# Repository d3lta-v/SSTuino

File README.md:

Designed by FourierIndustries LLP | Designed, assembled and tested in Singapore

# SSTuino

SSTuino is an easy to use Wi-Fi enabled microcontroller, designed and fabricated by SST Alumni. Users can write programs to connect or control things over the Internet. It is derived from the SPEEEduino 1.1 with some improvements.

**SSTuino Official Website: [https://sstuino.fourier.industries](https://sstuino.fourier.industries)**

Related projects:

* [SSTuino Companion Library](https://github.com/d3lta-v/SSTuino_Companion)
* [Ultra Light Wi-Fi Interface](https://github.com/d3lta-v/ULWI)
* [ESPblaster](https://github.com/d3lta-v/ESPblaster)

## Technical information

### Repository Layout

* **SSTuino**: EAGLE files for SSTuino
* **Image Assets**: Image assets for websites related to the SSTuino and markdown pages.

### Startup states table

This table controls the various startup states of the ESP8266-01 Wi-Fi module, which allows it to operate, or be reprogrammed with your custom firmware, or even be electrically isolated from the rest of the SSTuino entirely.

|  | GPIO0 (1) | GPIO2 (2) | ESP-RX connect to D4 (3) | ESP-TX connect to D2 (4) | ESP-RESET Button |
|---------|:---------:|:---------:|:---------:|:---------:|:---------:|
| Wi-Fi Enable | ⬆️ | ⬆️ | ⬆️ | ⬆️ | Leave open |
| Disconnect ESP-01 | ❎ | ❎ | ⬇️ | ⬇️ | Leave open |
| Reset ESP-01 | ❎ | ❎ | ❎ | ❎ | Press down |
| Flash ESP-01 | ⬇️ | ⬆️ | ⬇️ | ⬇️ | Press down, set switches, release |

## Contributing

Contributing to the SSTuino Git Repository requires you to have EAGLE 8.4 or newer which supports Managed Libraries.

SSTuino primarily uses EAGLE's Managed Libraries made by Sparkfun, but also contain our own custom footprints and SMD component footprints from Cytron.

## Our team

* Chief Designer: Pan Ziyue ([@sammy0025](https://twitter.com/sammy0025))
* Assistants/Advisers: Goh Qian Zhe ([@QianZheGoh](https://twitter.com/QianZheGoh))
* The awesome folks at Arduino, Sparkfun and Adafruit for technical reference and ECAD models.

Open Source Hardware (OSHW)

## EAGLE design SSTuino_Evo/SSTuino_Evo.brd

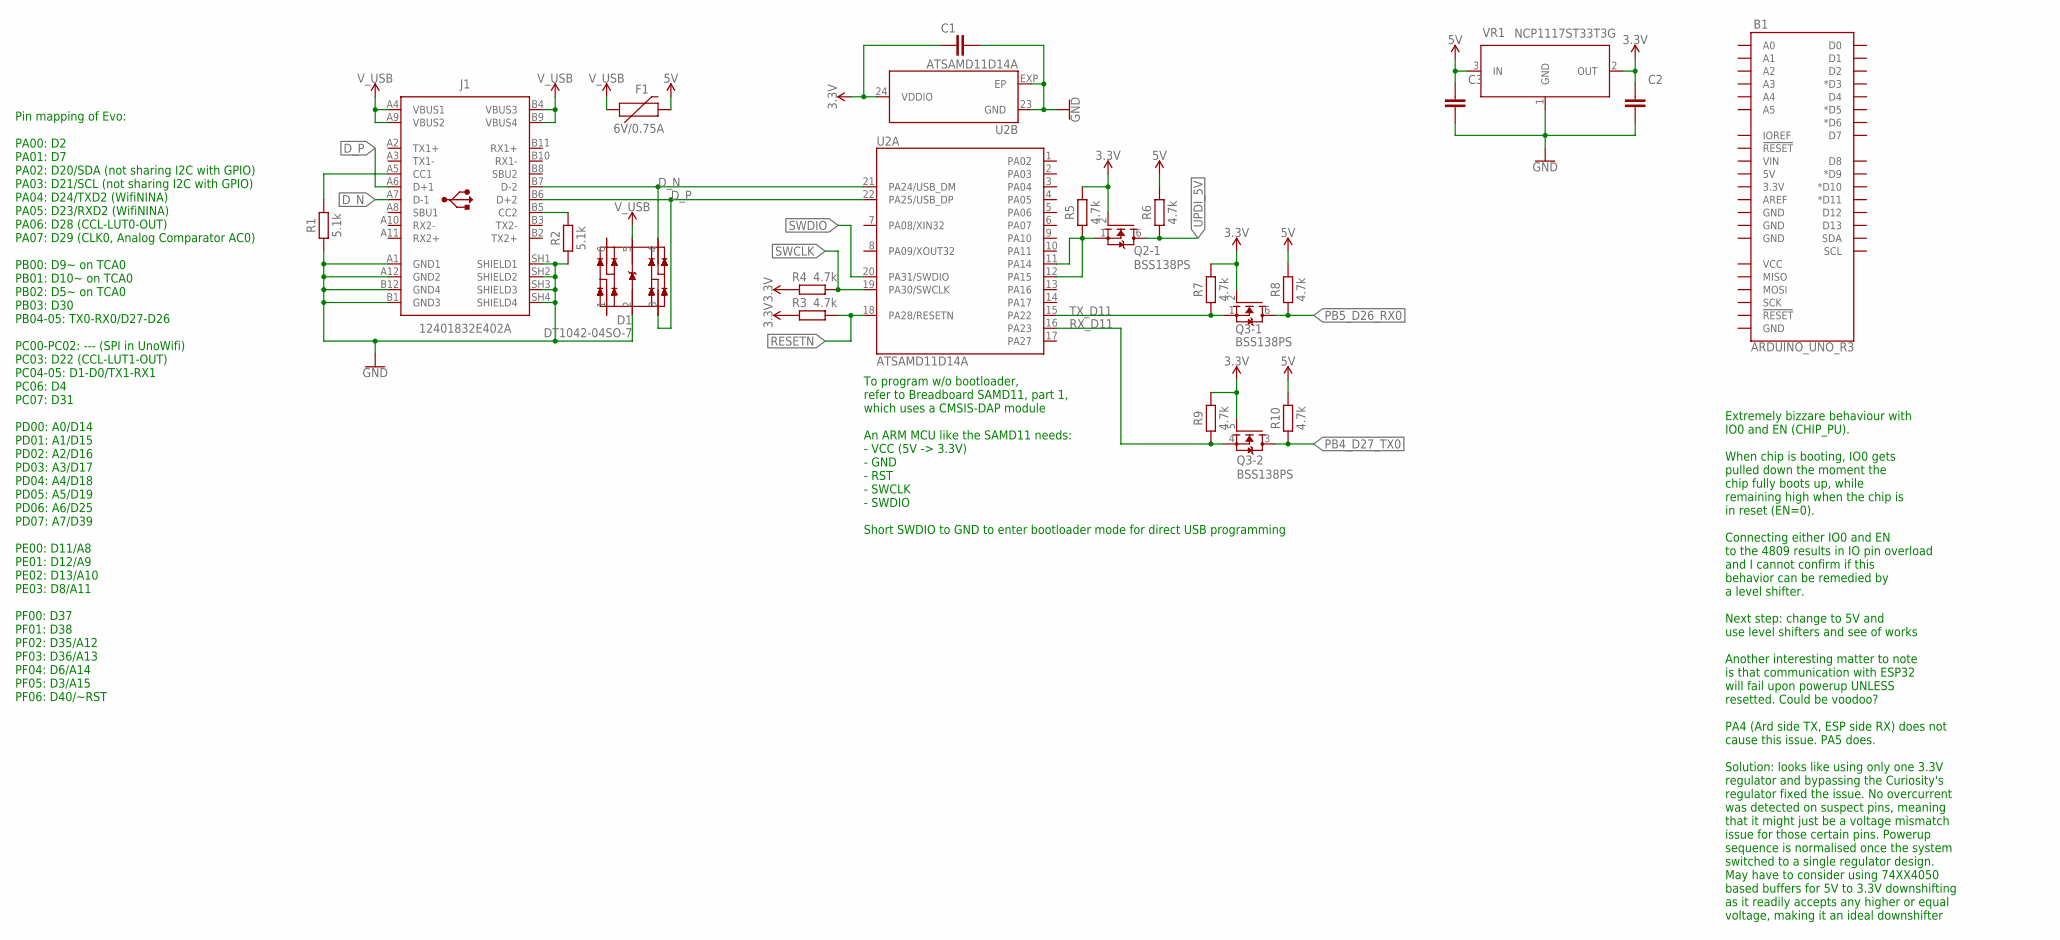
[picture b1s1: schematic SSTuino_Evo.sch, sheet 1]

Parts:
B1: ARDUINO_UNO_R3; ARDUINO_R3
C1: 100n; CAPC1005X60
C2, C3: 10uF; CAPC1608X85
D1: DT1042-04SO-7; SOT95P285X140-6N
F1: 6V/0.75A; 1206
J1: 12401832E402A
Q2, Q3: BSS138PS; ARDUINO-TRANSISTORS_SOT363
R1, R2: 5.1k; RESC1005X40
R3, R4, R5, R6, R7, R8, R9, R10: 4.7k; RESC1005X40
U2: ATSAMD11D14A; ARDUINO-UCS&SOCS_HVQFN24
VR1: NCP1117ST33T3G; SOT230P700X170-4

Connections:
3.3V: C1.1, C2.1, Q2.2 (G), Q3.2 (G), Q3.5 (G), R3.2, R4.2, R5.2, R7.2, R9.2, U2.24 (VDDIO), VR1.2 (OUT); also elsewhere on the board
5V: C3.1, F1.2, R6.2, R8.2, R10.2, VR1.3 (IN); also elsewhere on the board
CC1: J1.A5 (CC1), R1.2
CC2: J1.B5 (CC2), R2.2
D_N: D1.4 (IO3), J1.A7 (D-1), J1.B7 (D-2), U2.21 (PA24/USB_DM)
D_P: D1.3 (IO2), J1.A6 (D+1), J1.B6 (D+2), U2.22 (PA25/USB_DP)
GND: C1.2, C2.2, C3.2, D1.2 (VSS), J1.A1 (GND1), J1.A12 (GND2), J1.B1 (GND3), J1.B12 (GND4), J1.SH1 (SHIELD1), J1.SH2 (SHIELD2), J1.SH3 (SHIELD3), J1.SH4 (SHIELD4), R1.1, R2.1, U2.23 (GND), U2.EXP (EP), VR1.1 (GND); also elsewhere on the board
PB4_D27_TX0: Q3.3 (D), R10.1; also elsewhere on the board
PB5_D26_RX0: Q3.6 (D), R8.1; also elsewhere on the board
RESETN: R3.1, U2.18 (PA28/RESETN)
RX_D11: Q3.4 (S), R9.1, U2.16 (PA23)
SWCLK: R4.1, U2.19 (PA30/SWCLK)
SWDIO: U2.20 (PA31/SWDIO)
TX_D11: Q3.1 (S), R7.1, U2.15 (PA22)
UPDI_3V3: Q2.1 (S), R5.1, U2.11 (PA14), U2.12 (PA15)
UPDI_5V: Q2.6 (D), R6.1
V_USB: D1.5 (VCC), F1.1, J1.A4 (VBUS1), J1.A9 (VBUS2), J1.B4 (VBUS3), J1.B9 (VBUS4)

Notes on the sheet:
Pin mapping of Evo: PA00: D2 PA01: D7 PA02: D20/SDA (not sharing I2C with GPIO) PA03: D21/SCL (not sharing I2C with GPIO) PA04: D24/TXD2 (WifiNINA) PA05: D23/RXD2 (WifiNINA) PA06: D28 (CCL-LUT0-OUT) PA07: D29 (CLK0, Analog Comparator AC0) PB00: D9~ on TCA0 PB01: D10~ on TCA0 PB02: D5~ on TCA0 PB03: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
To program w/o bootloader, refer to Breadboard SAMD11, part 1, which uses a CMSIS-DAP module An ARM MCU like the SAMD11 needs: - VCC (5V -> 3.3V) - GND - RST - SWCLK - SWDIO Short SWDIO to GND to enter bootloader mode for direct USB programming
Extremely bizzare behaviour with IO0 and EN (CHIP_PU). When chip is booting, IO0 gets pulled down the moment the chip fully boots up, while remaining high when the chip is in reset (EN=0). Connecting either IO0 and EN to the 4809 results in IO pin overload and I cannot confirm if this behavior can 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

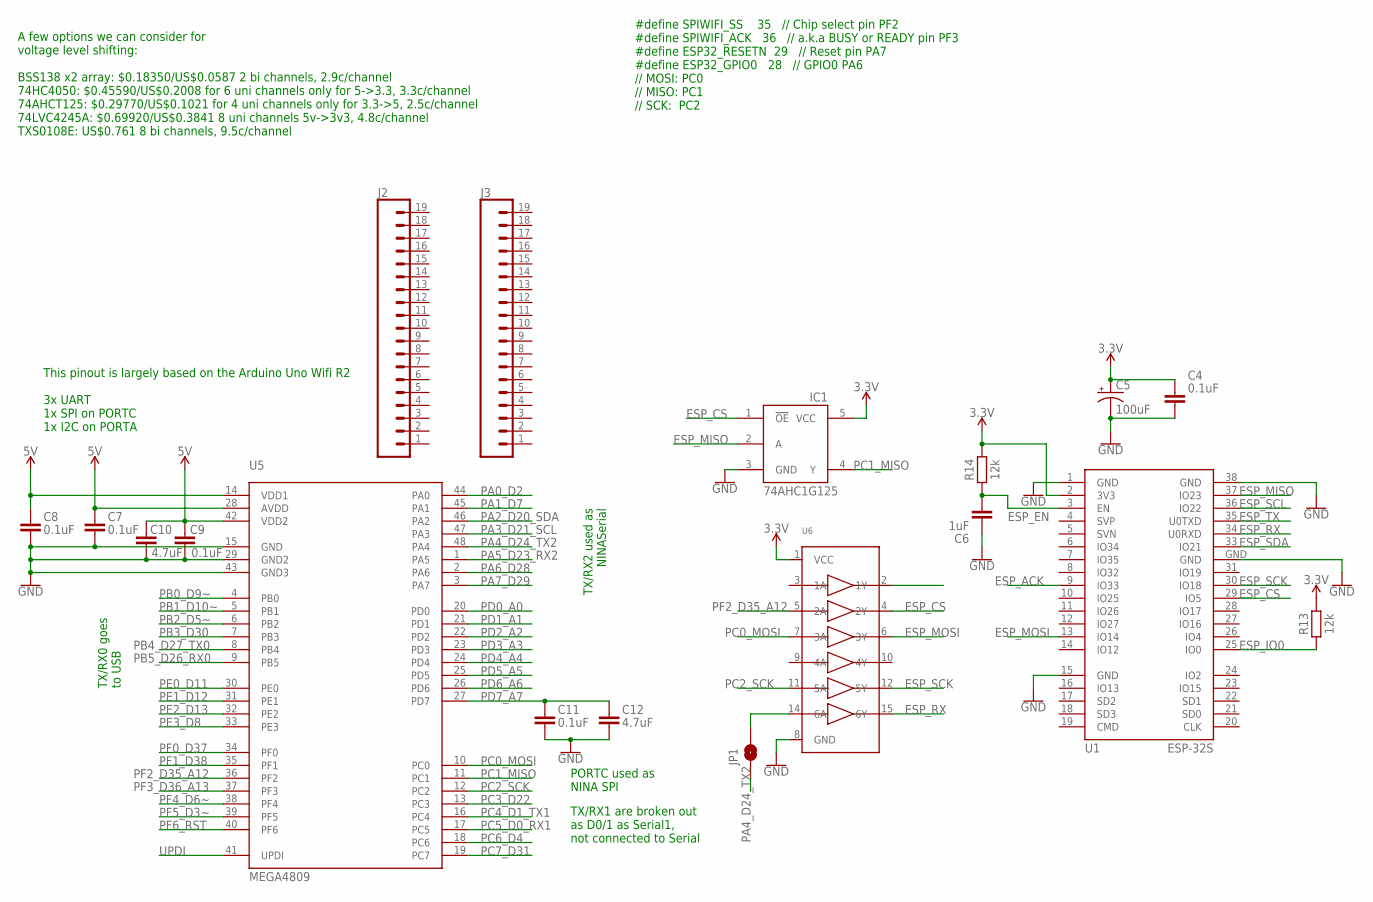
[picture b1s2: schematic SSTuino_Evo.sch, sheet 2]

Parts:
C4, C7, C8, C9, C11: 0.1uF; CAPC1005X60
C5: 100uF; CAPMP3216X180N
C6: 1uF; CAPC1005X60
C10, C12: 4.7uF; CAPC1005X60
IC1: 74AHC1G125; SOT23-5L
J2, J3: CONN_191X19_NO_SILK; 1X19_NO_SILK
JP1: JUMPER-SMT_2_NO_SILK; SMT-JUMPER_2_NO_SILK
R13, R14: 12k; RESC1005X40
U1: ESP-32S
U5: MEGA4809; TQFP48
U6: 74HC4050DTSSOP; TSSOP16

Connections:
3.3V: C4.1, C5.1 (+), IC1.5 (VCC), R13.2, R14.2, U1.2 (3V3), U6.1 (VCC); also elsewhere on the board
5V: C7.1, C8.1, C9.1, C10.1, U5.14 (VDD1), U5.28 (AVDD), U5.42 (VDD2); also elsewhere on the board
ESP_ACK: U1.9 (IO33)
ESP_CS: IC1.1 (!OE), U1.29 (IO5), U6.4 (2Y)
ESP_EN: C6.2, R14.1, U1.3 (EN)
ESP_IO0: R13.1, U1.25 (IO0)
ESP_MISO: IC1.2 (A), U1.37 (IO23)
ESP_MOSI: U1.13 (IO14), U6.6 (3Y)
ESP_RX: U1.34 (U0RXD), U6.15 (6Y)
ESP_SCK: U1.30 (IO18), U6.12 (5Y)
ESP_SCL: U1.36 (IO22)
ESP_SDA: U1.33 (IO21)
ESP_TX: U1.35 (U0TXD)
GND: C4.2, C5.2 (-), C6.1, C7.2, C8.2, C9.2, C10.2, C11.2, C12.2, IC1.3 (GND), U1.1 (GND), U1.15 (GND), U1.38 (GND), U1.GND, U5.15 (GND), U5.29 (GND2), U5.43 (GND3), U6.8 (GND); also elsewhere on the board
unnamed: JP1.2, U6.14 (6A)
PA0_D2: U5.44 (PA0)
PA1_D7: U5.45 (PA1)
PA2_D20_SDA: U5.46 (PA2)
PA3_D21_SCL: U5.47 (PA3)
PA4_D24_TX2: JP1.1, U5.48 (PA4)
PA5_D23_RX2: U5.1 (PA5)
PA6_D28: U5.2 (PA6)
PA7_D29: U5.3 (PA7)
PB0_D9~: U5.4 (PB0)
PB1_D10~: U5.5 (PB1)
PB2_D5~: U5.6 (PB2)
PB3_D30: U5.7 (PB3)
PB4_D27_TX0: U5.8 (PB4); also elsewhere on the board
PB5_D26_RX0: U5.9 (PB5); also elsewhere on the board
PC0_MOSI: U5.10 (PC0), U6.7 (3A)
PC1_MISO: IC1.4 (Y), U5.11 (PC1)
PC2_SCK: U5.12 (PC2), U6.11 (5A)
PC3_D22: U5.13 (PC3)
PC4_D1_TX1: U5.16 (PC4)
PC5_D0_RX1: U5.17 (PC5)
PC6_D4: U5.18 (PC6)
PC7_D31: U5.19 (PC7)
PD0_A0: U5.20 (PD0)
PD1_A1: U5.21 (PD1)
PD2_A2: U5.22 (PD2)
PD3_A3: U5.23 (PD3)
PD4_A4: U5.24 (PD4)
PD5_A5: U5.25 (PD5)
PD6_A6: U5.26 (PD6)
PD7_A7: C11.1, C12.1, U5.27 (PD7)
PE0_D11: U5.30 (PE0)
PE1_D12: U5.31 (PE1)
PE2_D13: U5.32 (PE2)
PE3_D8: U5.33 (PE3)
PF0_D37: U5.34 (PF0)
PF1_D38: U5.35 (PF1)
PF2_D35_A12: U5.36 (PF2), U6.5 (2A)
PF3_D36_A13: U5.37 (PF3)
PF4_D6~: U5.38 (PF4)
PF5_D3~: U5.39 (PF5)
PF6_RST: U5.40 (PF6)
UPDI: U5.41 (UPDI)

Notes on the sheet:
A few options we can consider for voltage level shifting: BSS138 x2 array: $0.18350/US$0.0587 2 bi channels, 2.9c/channel 74HC4050: $0.45590/US$0.2008 for 6 uni channels only for 5->3.3, 3.3c/channel 74AHCT125: $0.29770/US$0.1021 for 4 uni channels only for 3.3->5, 2.5c/channel 74LVC4245A: $0.69920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
This pinout is largely based on the Arduino Uno Wifi R2 3x UART 1x SPI on PORTC 1x I2C on PORTA
TX/RX2 used as NINASerial
PORTC used as NINA SPI
TX/RX1 are broken out as D0/1 as Serial1, not connected to Serial
TX/RX0 goes to USB
#define SPIWIFI_SS 35 // Chip select pin PF2 #define SPIWIFI_ACK 36 // a.k.a BUSY or READY pin PF3 #define ESP32_RESETN 29 // Reset pin PA7 #define ESP32_GPIO0 28 // GPIO0 PA6 // MOSI: PC0 // MISO: PC1 // SCK: PC2

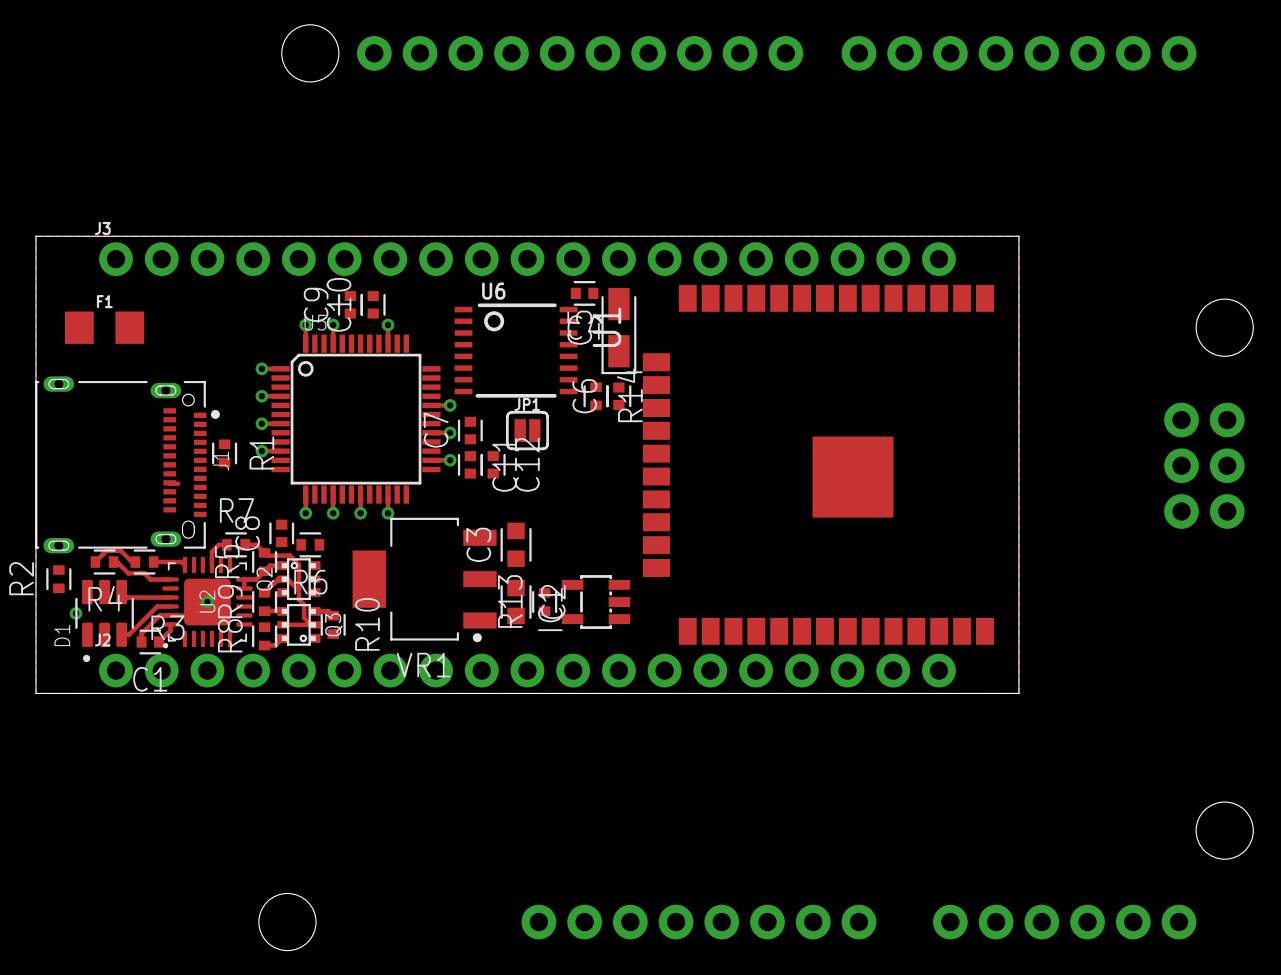
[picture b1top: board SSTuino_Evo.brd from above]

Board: 2 copper layers, 54.6 x 25.4 mm, 39 parts (0 on the bottom side), 30 nets.

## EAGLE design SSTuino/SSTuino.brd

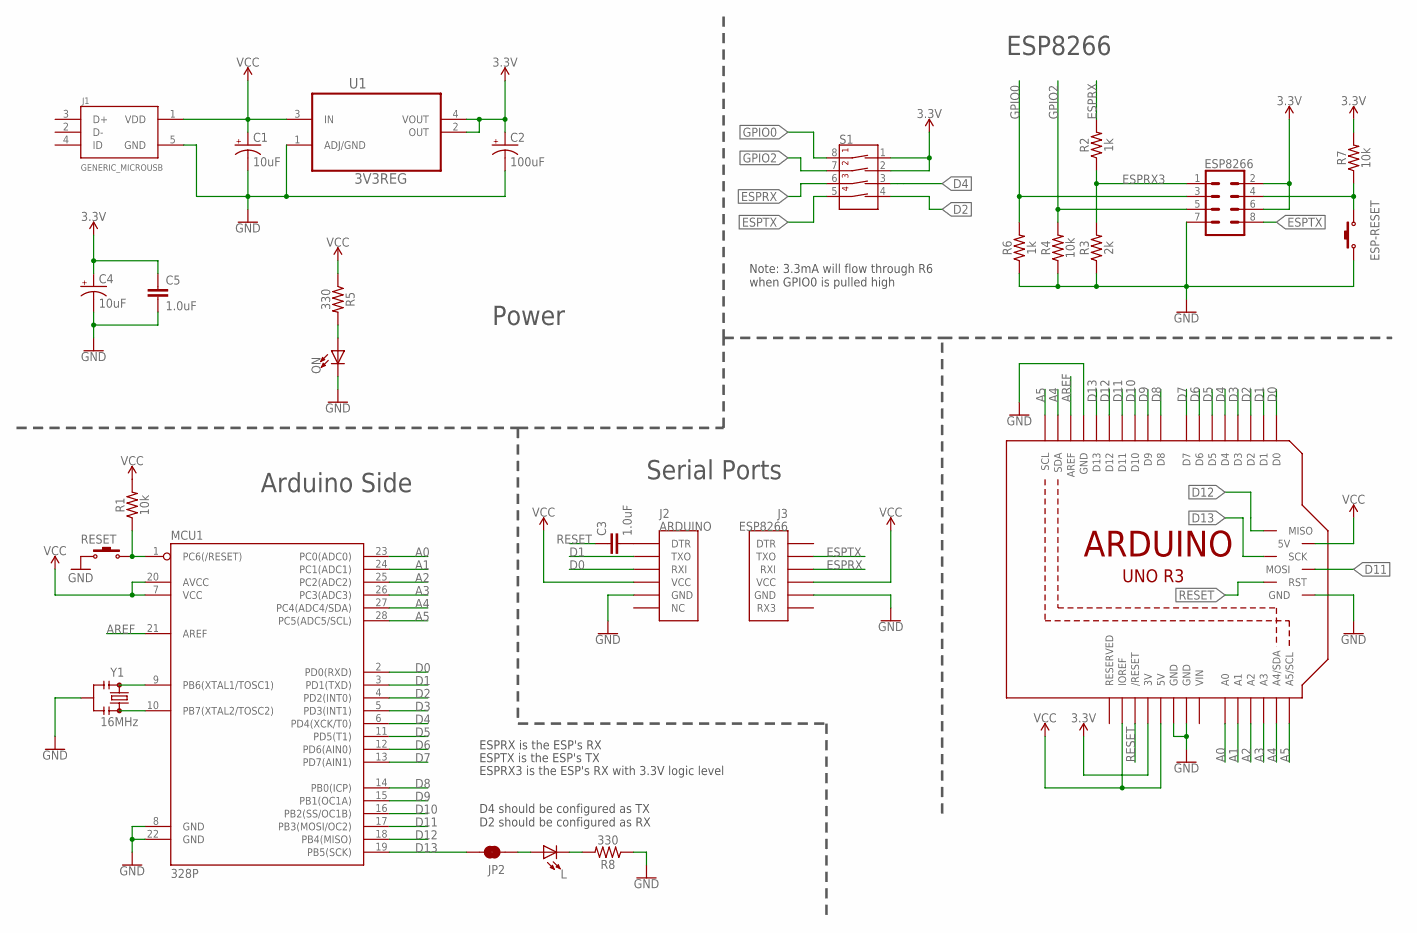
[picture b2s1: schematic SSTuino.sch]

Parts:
C1: 10uF; EIA3528
C2: 100uF; PANASONIC_D
C3, C5: 1.0uF; 1206
C4: 10uF; EIA3216
ESP8266: CONN_04X2; 2X4
ESP-RESET: SW-PB_(KAN0641); S-SP-4N-KAN0641
J1: GENERIC_MICROUSB; FRAMATOME_10118194-0001LF
J2: ARDUINO; CP2102_DEVICE_MICROUSB
J3: ESP8266; CP2102_DEVICE_MICROUSB_ESP8266
JP2: JUMPER-SMT_2_NC_TRACE_SILK; SMT-JUMPER_2_NC_TRACE_SILK
L: LED3MM
M1: ARDUINO_R3_ICSPSST; ARDUINOR3_ISCP_SST
MCU1: 328P; DIP28
ON: LED3MM
R1, R4, R7: 10k; 1206
R2, R6: 1k; 1206
R3: 2k; 1206
R5, R8: 330; 1206
RESET: SW-PB_(KAN0641); S-SP-4N-KAN0641
S1: DIP-04SMD; DIPSWITCH-04-SMD
U1: 3V3REG; SOT230P696X180-4N
Y1: 16MHz; RESONATOR-SMD-3.2X1.3

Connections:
3.3V: C2.+, C4.+, C5.1, ESP8266.2, ESP8266.6, M1.3V, R7.2, S1.1 (1A), S1.2 (2A), U1.2 (OUT), U1.4 (VOUT)
A0: M1.A0, MCU1.23 (PC0(ADC0))
A1: M1.A1, MCU1.24 (PC1(ADC1))
A2: M1.A2, MCU1.25 (PC2(ADC2))
A3: M1.A3, MCU1.26 (PC3(ADC3))
A4: M1.A4 (A4/SDA), M1.SDA, MCU1.27 (PC4(ADC4/SDA))
A5: M1.A5 (A5/SCL), M1.SCL, MCU1.28 (PC5(ADC5/SCL))
AREF: M1.AREF, MCU1.21 (AREF)
D0: J2.RXI, M1.D0, MCU1.2 (PD0(RXD))
D1: J2.TXO, M1.D1, MCU1.3 (PD1(TXD))
D2: M1.D2, MCU1.4 (PD2(INT0)), S1.4 (4A)
D3: M1.D3, MCU1.5 (PD3(INT1))
D4: M1.D4, MCU1.6 (PD4(XCK/T0)), S1.3 (3A)
D5: M1.D5, MCU1.11 (PD5(T1))
D6: M1.D6, MCU1.12 (PD6(AIN0))
D7: M1.D7, MCU1.13 (PD7(AIN1))
D8: M1.D8, MCU1.14 (PB0(ICP))
D9: M1.D9, MCU1.15 (PB1(OC1A))
D10: M1.D10, MCU1.16 (PB2(SS/OC1B))
D11: M1.D11, M1.MOSI, MCU1.17 (PB3(MOSI/OC2))
D12: M1.D12, M1.MISO, MCU1.18 (PB4(MISO))
D13: JP2.2, M1.D13, M1.SCK, MCU1.19 (PB5(SCK))
DTR: C3.2, J2.DTR
ESPRESET: ESP8266.4, ESP-RESET.3 (2), ESP-RESET.4 (2), R7.1
ESPRX: J3.P$4 (RXI), R2.2, S1.6 (3B)
ESPRX3: ESP8266.1, R2.1, R3.2
ESPTX: ESP8266.8, J3.P$3 (TXO), S1.5 (4B)
GND: C1.C (-), C2.-, C4.-, C5.2, ESP8266.7, ESP-RESET.1, ESP-RESET.2 (1), J1.5 (GND), J2.GND, J3.P$5 (GND), M1.GND, M1.GND@1 (GND), M1.GND@2 (GND), M1.GND@3 (GND), MCU1.8 (GND), MCU1.22 (GND), ON.K (C), R3.1, R4.1, R6.1, R8.1, RESET.1, RESET.2 (1), U1.1 (ADJ/GND), Y1.2
GPIO0: ESP8266.3, R6.2, S1.8 (1B)
GPIO2: ESP8266.5, R4.2, S1.7 (2B)
unnamed: MCU1.10 (PB7(XTAL2/TOSC2)), Y1.3
unnamed: L.K (C), R8.2
unnamed: JP2.1, L.A
unnamed: ON.A, R5.2
unnamed: MCU1.9 (PB6(XTAL1/TOSC1)), Y1.1
RESET: C3.1, M1.RESET (/RESET), M1.RESET_ICSP (RST), MCU1.1 (PC6(/RESET)), R1.1, RESET.3 (2), RESET.4 (2)
VCC: C1.A (+), J1.1 (VDD), J2.5V (VCC), J3.P$6 (VCC), M1.5V, M1.5V_ICSP (5V), M1.IOREF, MCU1.7 (VCC), MCU1.20 (AVCC), R1.2, R5.1, U1.3 (IN)
VIN: M1.VIN

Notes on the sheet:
ESPRX is the ESP's RX
ESPTX is the ESP's TX
D4 should be configured as TX D2 should be configured as RX
ESPRX3 is the ESP's RX with 3.3V logic level
Power
Arduino Side
Serial Ports
ESP8266
Note: 3.3mA will flow through R6 when GPIO0 is pulled high

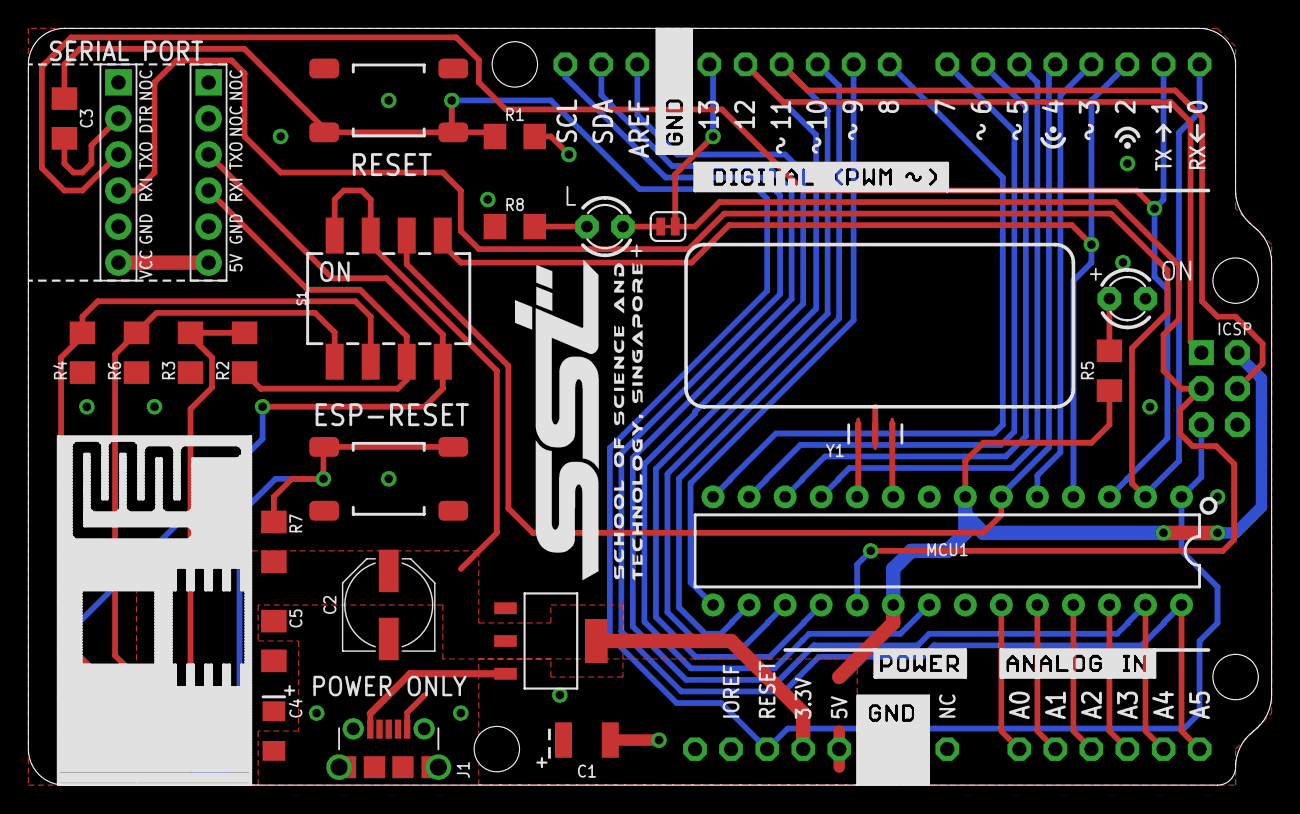
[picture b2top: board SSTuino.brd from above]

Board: 2 copper layers, 87.6 x 53.3 mm, 30 parts (0 on the bottom side), 37 nets.

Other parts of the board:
U$1: ESP8266-NEGASILK
U$2: SST-MED
U$3: SST-HEXAGON-INV-BMP

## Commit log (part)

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2019-07-01 added analytics to page
2019-07-01 added global site tag
2019-07-03 created thunkable.md for lessons involving thunkable
2019-07-03 test
2019-07-03 updated thunkable.md with content
2019-07-03 updated content for thunkable.md
2019-07-03 added tinkercad.md
2019-07-03 updated content of tinkercad.md
2019-07-03 minor update to content of tinkercad.md
2019-07-03 edits made to the content of thunkable.md
2019-07-03 minor update to content in thunkable.md
2019-07-03 minor updates to tinkercad.md
2019-07-03 updated content from helloWorld.md
2019-07-03 upload of media for tinkercad tutorial
2019-07-03 fixed broken picture link for Social Provider segment
2019-07-03 attempt to fix broken lists
2019-07-03 fixed image sizing for sign in and social provider images
2019-07-03 fixed errata of list
2019-07-03 asdhapsdhaosdi
2019-07-05 minor formatting to content in temperature sensor section
2019-07-05 updated content for helloWorld.md
2019-07-05 minor update to formatting for helloWorld.md
2019-07-05 drafted new content headings in index.md
2019-07-08 added post.html for prototyping of tutorial pages
2019-07-08 updated header to new format
2019-07-08 trying out new layouts for tutorial pages
2019-07-08 fixed missing body and html tags at the bottom of the code
2019-07-08 deleted post.html and reverted formatting of addButton.md to last edit.
2019-07-08 created lessonIntro.md
2019-07-08 Updated index.md with new content (Link to lessonIntro.md)
2019-07-08 corrected erronus name
2019-07-08 creation of thunkableIntro.md, change of content in index and addition of assets
2019-07-08 Addition of assets for tutorial
2019-07-08 addition of image assets for thunkableIntro.md
2019-07-08 updated link for index.md
2019-07-08 updated image formatting in thunkableIntro.md
2019-07-08 creation of image assets
2019-07-08 insert images to thunkableIntro.md
2019-07-08 edited formatting of pictures
2019-07-08 fixed error in picture link
2019-07-08 edited formatting for image assets in thunkableIntro.md
2019-07-08 Updated content of thunkableIntro.md
2019-07-08 edited content in thunkableIntro.md
2019-07-08 Updated content in thunkableIntro.md
2019-07-08 creation of thunkableSpicing.md
2019-07-08 added electronicBasics.md and edited content of tinkercad.md
2019-07-08 minor edits to formatting
2019-07-08 added content in electronicBasics.md
2019-07-08 updated content and formatting of electronicBasics.md
2019-07-08 added link to electronicBasics.html in index.md
2019-07-08 updated content of electronicBasis.md
2019-07-08 updated formatting for attached image asset
2019-07-10 updated content in tinkercad.d
2019-07-10 added link to index.md
2019-07-10 updated content for electronicBasics.md with a gif from sparkfun lmao
2019-07-10 updated content for electronicBasics.md
2019-07-10 added content to electronicBasics.md
2019-07-11 fixed error in link
2019-07-12 Updated content for tinkercad.md
2019-07-15 Moved content from partsList.md to electronicBasics.md to reduce confusion in the future.
2019-07-15 added content from partsList.md to reduce confusion
2019-07-16 Updated content and testing out linking headers
2019-07-16 edited resistor content in electronicBasics.md
2019-07-16 Shifted breadboard content
2019-07-16 testing of headers
2019-07-16 fixed header link for LED
2019-07-16 Reorganised content in electronicBasics.md
2019-07-16 Updated table of contents for electronicBascis.md
2019-07-16 fixed error in header link
2019-07-16 lmao
2019-07-16 Updated index.md to include a interest form
2019-07-16 Updated formatting for link in index.md
2019-07-16 Updated content for supportr and contace
2019-07-16 removed section about changes
2019-07-16 Upload of resistor pictures
2019-07-16 Insertion of media for metal and carbon resistor comparison
2019-07-17 Upload of image assets for tutorial
2019-07-17 Updated content of electronicBasics.md
2019-07-17 Updated content in electronicBasics.md
2019-07-17 updated for useful Links page
2019-07-17 updated links for links
2019-07-17 Updated content for links.md
2019-07-18 updated links.md
2019-07-18 Upload of image assets
2019-07-18 Updated content in tinkercad.md
2019-07-18 Updated errenous picture links in tinkercad.md
2019-07-18 Updated content and formatting for tinkercad.md
2019-07-18 Updated content of sstuinoProgram.md
2019-07-18 Updated index.md to include the new sstuinoProgram.md link
2019-07-18 Updated tinkercad.md with link to sstuinoProgram.md
2019-07-18 fixed broken link
2019-07-18 SSTuino preview updated
2019-07-19 Updated content for sstuinoProgram.md
2019-07-19 Updated content in sstuinoProgram.md
2019-07-19 Removed Sec1 index menu, due to tutorials being replaced
2019-07-19 update of content
2019-07-19 updated content for digitalRead.md
2019-07-19 fixed missing image asset in sstuinoProgram.md
2019-07-19 fixed bad formatting
2019-07-19 Updated digitalRead.md
2019-07-22 gif test
2019-07-22 Addition of gif for the tutorial
2019-07-22 fixed an error in formatting
2019-07-22 removal of redundant sec 1 index
2019-07-22 Update of media content
2019-07-22 Updated formatting for digitalRead.md
2019-07-22 Fixed bad formatting in digitalRead.md
2019-07-23 Update README.md
    Changed link for reference website to SSTuino Website
2019-07-23 Updated content for index.md
2019-07-24 Updated formatting
2019-07-24 Upload of media assets
2019-07-24 Wrote the basics of AND and OR operators and how they came about
2019-07-24 changed sentence and added logic gate link
2019-07-25 decided not to use B612 for development due to lack of slash with digit "0"
2019-07-25 updated content in digitalRead.md
2019-07-25 fixed wrong image asset in digitalRead.md
2019-08-01 updated content of digitalRead.md
2019-08-02 Updated content for digitalWrite.md
2019-08-02 create media content
2019-08-03 Add media content
2019-08-03 Updated erronous formatting in digitalRead.md
2019-08-08 removed unecessary tutorials and renamed tutorial
2019-08-08 updated content for dataInput.md
2019-08-12 fixed errornous formatting for image asset
2019-08-12 Updated content for dataInpud.md
2019-08-15 Updated content of dataInput.md
2019-08-28 Added a last minute thing lmao
2019-08-28 Updated ULWI getting started page
2019-08-28 Updated formatting for tutorial
2019-08-30 Updated content of index.md
2019-09-15 Added IoT tutorial
2019-09-15 updated content for tutorial
2019-09-15 Testing out embedding videos
2019-09-15 updated iot tutorial content
2019-09-15 updated content for iot tutorial
2019-09-15 testing html video
2019-09-15 Updated content for iot
2019-09-15 updated formatting for iot tutorial
2019-09-15 Updated content for sstuino iot
2019-09-15 fixed formatting issue
2019-09-17 Updated index to help with wayfinding
2019-09-17 Updated formatting for index
2019-09-17 Updated fomatting for index
2019-09-17 Updated content for index for better wayfinding
2019-09-18 fixed video alignment
2019-09-18 updated adafruit io video to autoplay
2019-09-18 fixed video
2019-09-18 fixed video dimensions
2019-09-18 Updated content of sstuinoIoT.md
2019-09-19 added Jekyll SEO plugin
2019-09-19 prevented SEO from messing with title
2019-09-19 Updated the iot tutorial content
2019-09-19 removed title from SEO
2019-09-19 testing jekyll seo configurations
2019-09-19 testing jekyll configuration
2019-09-19 edited seo tags
2019-09-19 Split actions on my fingertips to two sections to simplify tutorial
2019-09-19 Updated index.md to reflect the 2 split tutorials
2019-09-19 Updated title for sstuino iot tutorial
2019-09-20 revamped adafruit IO images location to relative
2019-09-20 converted some images to webp for testing
2019-09-20 minified pngs instead of using webp
2019-09-20 minified image sizes
2019-09-20 fixed video autoplay for iphone
2019-09-20 added gerber files
2019-09-20 changed company branding and added CNAME
2019-09-21 fixed minor issues with linking
2019-09-21 moved and renamed PNGs for Guide Images
2019-09-22 updated README for better SEO
2019-09-22 Updated SSTuino MQTT tutorial content, shifted image media to another folder
2019-09-22 Fixed broken image links for IoT Tutorial
2019-09-22 Picture editing for iot image assets
2019-09-22 Inserted code for iot tutorial
2019-09-22 Included custom settings to vertically scroll long code blocks
2019-09-22 Updated content of SSTuino IoT for Wifi Access
2019-09-23 Upload of iot images
2019-09-23 Updated tutorial content
2019-09-24 converted tutorials index.md to relative links
2019-09-24 deleted docs_backup
2019-09-24 updated content for iot documentation
2019-09-25 added library autoinstall script
2019-09-25 shifted content in iot tutorial
2019-09-25 Added subscribe content for iot tutorial
2019-09-25 Changed small to medium for formatting image
2019-09-25 Updated internet of things content
2019-09-25 edited library installation script name
2019-09-25 suppressed unzip messages
2019-09-25 changed library installation procedure to purely terminal based and improved installation script to halt on errors
2019-09-29 Updated tutorial content for sstuinoIoT.md
2019-09-30 Updated content of iot tutorial
2019-09-30 Added additional content for iot tutorial
2019-09-30 Updated index page for page chapters
2019-09-30 fixed link to thunkable template
2019-10-04 Will remove setting up of adafruit account and instead link to adafruit's own tutorial
2019-10-04 Updated table of contents for SSTuinoIot
2019-10-04 removed adafruitio.md and combined iot tutorial into one page.
    Setting up of adafruit io account will be done using the Adafruit's docs instead.
2019-10-10 deleted index backup and started to add in table of contents to tutorial pages
2019-10-10 Fixed formatting issue in index
2019-10-10 Updated index with additional tutorials
2019-10-18 Updated parts list for 2020 batch
2019-10-18 Updated the parts list and electronic basics page for 2020 batch of SSTuinos
2019-10-18 Fixed error in spelling
2019-10-21 updated content
2019-10-25 Updated getting started tutorial
2019-10-25 fixed formatting issues
2019-10-26 Updated parts list
2019-10-26 updated image asset locations
2019-10-26 Updated image links for tutorial
2019-10-26 Updated links for table of contents
2019-10-26 Updated electronic basics for 2020 kit
2020-09-21 Added the instalation of the SSTuino Companion Library to the GettingStarted page
2020-10-29 changed partslist
2020-10-29 updated partslist picture
2020-10-29 Edited content in ElectronicBasics.md
2020-10-29 changed RGB led image size for ElectronicBasics
2021-01-15 Update partsList.md
    Updated amount of RGB LEDs included with the kit
2021-04-09 fixed broken library reference
2021-06-10 modified EVO
2021-06-27 last update before routing

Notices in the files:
parts and their libraries:
SparkFun-Capacitors: Licensing: Creative Commons ShareAlike 4.0 International - https://creativecommons.org/licenses/by-sa/4.0
esp32: Creative Commons Attribution-ShareAlike 4.0 International
